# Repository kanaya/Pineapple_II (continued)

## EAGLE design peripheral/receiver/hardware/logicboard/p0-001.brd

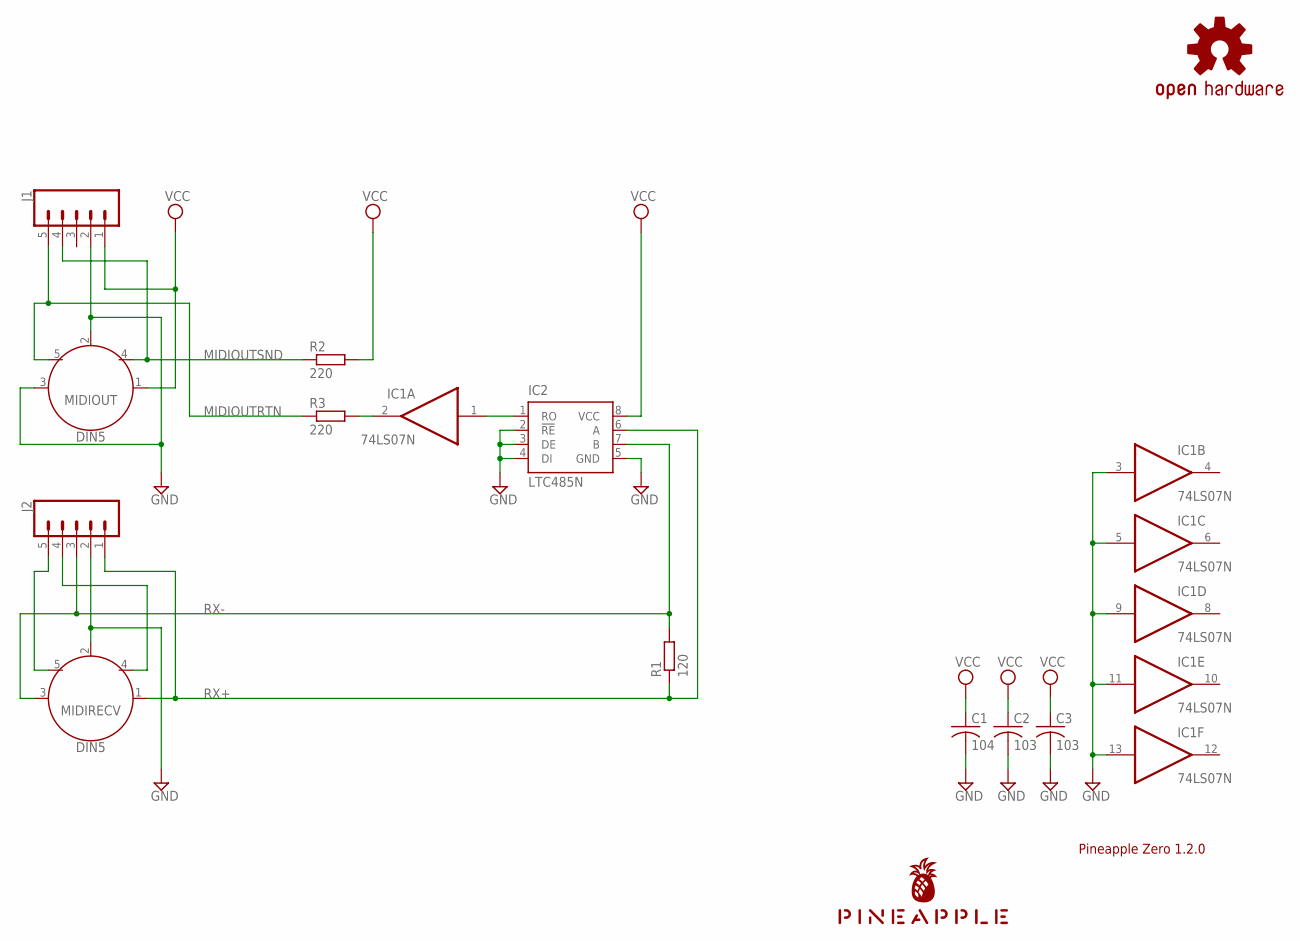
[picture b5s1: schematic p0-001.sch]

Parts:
C1: 104; C025-025X050
C2, C3: 103; C025-025X050
IC1: 74LS07N; DIL14
IC2: LTC485N; DIL08
J1, J2: CONN_05JST; JST-5-PTH
LOGO1: OSHW-LOGOS-COPPER; OSHW-LOGO-S_COPPER
MIDIOUT: DIN5; DIN5-RA-PTH
MIDIRECV: DIN5; DIN5-RA-PTH
R1: 120; 0204/5
R2, R3: 220; 0204/5
U$1: PINEAPPLE450

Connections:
DUMMY4: J2.4, MIDIRECV.4
DUMMY5: J2.5, MIDIRECV.5
GND: C1.2, C2.2, C3.2, IC1.3 (I), IC1.5 (I), IC1.7 (GND), IC1.9 (I), IC1.11 (I), IC1.13 (I), IC2.2 (!RE), IC2.3 (DE), IC2.4 (DI), IC2.5 (GND), J1.2, J2.2, MIDIOUT.2, MIDIOUT.3, MIDIRECV.2
MIDIOUTRTN: J1.5, MIDIOUT.5, R3.1
MIDIOUTSND: J1.4, MIDIOUT.4, R2.1
unnamed: IC1.2 (O), R3.2
RX+: IC2.6 (A), J2.1, MIDIRECV.1, R1.1
RX-: IC2.7 (B), J2.3, MIDIRECV.3, R1.2
TX: IC1.1 (I), IC2.1 (RO)
VCC: C1.1, C2.1, C3.1, IC1.14 (VCC), IC2.8 (VCC), J1.1, MIDIOUT.1, R2.2

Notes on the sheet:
Pineapple Zero 1.2.0

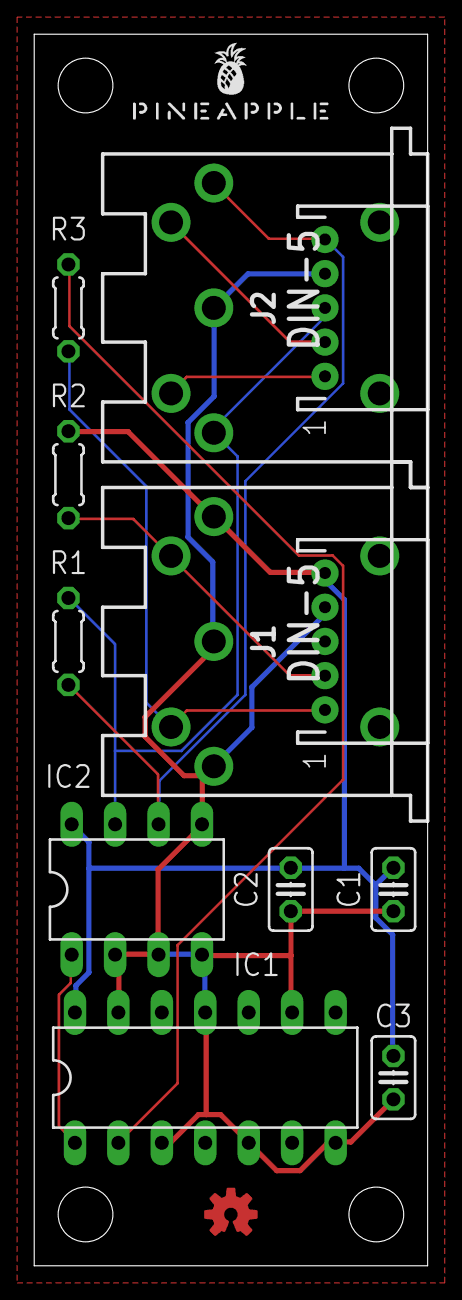
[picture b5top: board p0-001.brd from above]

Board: 2 copper layers, 23.0 x 72.0 mm, 14 parts (0 on the bottom side), 10 nets.

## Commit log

2020-01-31 Copied 2.0.0-X1 from the old repo.
2020-01-31 Added .gitignore.
2020-01-31 Changed panel design.
2020-01-31 New design for 2.0.1.
2020-01-31 Readability.
2020-01-31 Silk.
2020-02-01 Fixed power supply.
2020-02-08 Fixed position of large capacitors.
2020-02-09 Unified all buses.
2020-02-09 Now front LED is bi-color.
2020-02-09 PH connector.
2020-02-09 Document.
2020-02-09 Document update.
2020-02-09 Now pin 3 of MIDI In+ is connected to PUP pin.
2020-02-10 MIDI In detector.
2020-02-10 Added MIDI receiver unit.
2020-02-11 Moved peripheral dir to the top.
2020-02-12 Now U1 can be ether 1-Wire or Analog thermal sensor.
2020-02-12 Pin 25 of Front Connector is now connected to LED0.
2020-02-12 Document update for pull-down version.
2020-02-12 Now the sensors are connected to pull-down resistors.
2020-02-12 Silk and document.
2020-02-13 Qwiic (3.3V I2C) connector and signal level converter at the back surface.
2020-02-13 DC-In connector.
2020-02-14 Fine tune of silk.
2020-02-14 Set vRestrict zones.
2020-02-14 Changed vRestricted zones.
2020-02-14 Routed.
2020-02-14 Minor change of silk and vRestrict zones.
2020-02-14 Qwiic 5V.
2020-02-18 Pull up of RX.
2020-02-18 Pinhead for Relay.
2020-02-29 Clean up of document, schematic, and board design.
2020-02-29 Name of signal.
2020-03-01 GND net.
2020-03-23 Now MIDI In+ has Aux pin.
2020-03-24 Pull-down resistor from 100 to 10k.
2020-03-24 Changed pinout of Display port.
2020-04-18 F25 is now connected to AREF.
2020-04-19 Reflesh.
2020-04-21 Reflesh...
2020-04-27 Making...
2020-04-28 Now front port is Pineapple IIc compatible.
2020-04-29 Replacing.
2020-04-30 Refine.
2020-05-06 Renumbered number of jumpers.
2020-05-06 Now Vcc is directly connected to the regulator.
2020-05-07 Changed resistance attached to LED.
2020-05-07 Changed position of capacitors.
2020-05-11 Designing.
2020-05-11 Placed RTC board.
2020-05-11 To be renumbered.
2020-05-11 Renumbered.
2020-05-12 Fixed part numbers and silks.
2020-05-12 Fixed silk.
2020-05-12 Fixed pattern of RTC.
2020-05-13 Removed RLY con. Removed +9V con. Added I2C and Vdd con.
2020-05-13 Changed connectors of longrange receiver.
2020-05-15 Yeah!
2020-05-16 Looks good.
2020-05-17 First try.
2020-05-17 Fixed some error.
2020-05-19 New display connector.
2020-05-19 Re-design.
2020-05-19 Removed bus.
2020-05-19 A little bit better.
2020-05-20 Redesign...
2020-05-20 Rough design. Looks okay.
2020-06-02 Changed power supply.
2020-06-03 Added power selector.
2020-06-04 Added relay-out connector (again).
2020-06-28 Rounded corners.
2020-07-06 Added Vin mark on the board.
2020-07-08 Added Power-Grid.
2020-07-09 Power Grid 2.
2020-07-09 Swapped Vcc and Vcc/2.
2020-07-11 Fixed some errors.
2020-07-11 Changed Relay port and Alt. Power port.
2020-07-15 List of components.
2020-09-03 Added pads to connect MIDI IN and RX.
2020-09-03 Renumbered connectors. Fixed error of silk pattern.
2020-09-03 Update document.
2020-09-03 Fixed LED numbers.
2020-09-03 Simulation of Arduino Nano and Portena.
2020-09-03 Clean up of schematic.
2020-09-04 Moved resistor net up.
2020-09-18 Added LED pins. Changed pin number of LED connectors.
2020-09-24 Now B5 is connected to LED0 signal.
2020-09-24 B05 is connected to LED0A (not LED0).
2020-09-25 Analog input pins are now directly connected to pull-down resistor. Sensor pins are connected to analog input pins through analog switches. AREF is now connected to Vcc/2.
2020-09-25 Fixed AREF. Changed PWR connector. Etc.
2020-12-11 Test.
2021-02-16 Fixed pinout.
2021-02-18 Added SPI connector.
2021-02-19 Changed power pin from GND-Vcc to Vcc-GND-V+.
2021-02-19 Silk. (Tentative)
2021-02-22 Changed front-bus and SPI bus.
2021-02-24 Created P20 (port replicator) schematic and artwork.
2021-02-24 Cleared unnecessary parts.
2021-02-24 Parts only. No connection.
2021-02-24 The first artwork for MIDI Port Replicator.
2021-02-24 Re-arrange of net resistors.
2021-02-24 Silk of board.
2021-02-24 Remake of port rep.
2021-02-24 Hmm...
2021-02-24 Fix of _main_ logic board.
2021-02-24 Trying to implement a port replicator.
2021-02-24 Initial layout.
2021-02-27 Design of the port replicator.
2021-03-01 Silk mark for MIDI-IN.
2021-03-01 Silk mark for MIDI OUT.
2021-03-01 Approved warnings and added silk pattern for Vdd.
2021-03-01 Port replicator.
2021-03-05 Changed revision name to 2.1.0-RELEASE.
2021-03-08 Version of MIDI-IN, MIDI-THRU, and SPI only.
2021-03-08 Writing.
2021-03-08 Wiring.
2021-03-09 First working version of MIDI IN, MIDI THRU, SPI edition.
2021-03-09 Set restricted zones to left and right edges.
2021-03-09 GND.
2021-03-09 Arrangement of some parts (P20).
2021-03-10 DIP SW.
2021-03-10 Removed PWR pins.
2021-03-10 Clean up.
2021-03-13 JP5 is now compatible with Euroblock.
2021-03-13 The port replicator now has euroblock terminal.
2021-03-13 Renewal of Port Replicator.
2021-03-16 Moved relay port.
2021-03-18 Stepper Driver v0.0.2-X.
2021-03-19 Second try.
2021-03-20 TLP552 -> TLP2630.
2021-03-21 Pads to close V+ and Vin.
2021-03-26 Updated backside port to 2.0.
2021-03-27 Copied P2-001 to P2-003.
2021-03-28 Very rough but should be okay.
2021-03-28 Hotfix of the original P2.
2021-03-28 Configuring.
2021-03-29 Hotfix of relay connector (P2).
2021-03-29 First try. Should work. Need to renumber and rename parts.
2021-03-29 Renumbered some connectors.
2021-03-29 Moved Pineapple IIb to an independent repo.
2021-03-30 Flipped V+-Vin pads.
2021-03-30 Removed SE/Lucent-P1.
2021-04-02 Swapped MIDI RX+ and MIDI RX DETECT.
2021-04-02 Renumbered parts of Port Replicator.
2021-04-06 Fixed unconnected bus.
2021-04-10 Redesign of port rep.
2021-04-10 Renumbered parts of Pineapple II.
2021-04-10 Renumbered parts of Pineapple II and port rep.
2021-04-10 Renumbered Qwiic connectors.
2021-04-10 LED -> L.
2021-05-03 Fixed DTCT circuits.
2021-05-19 Silk for the lot number 2. Added Gerber.
2021-10-31 Now power has 12mil width and superpower has 24mil width.
2021-10-31 Power has 20mil width and superpower has 40mil width.
2021-10-31 Updated backport pintouts of port rep.
2021-10-31 Fixed netclasses.
2021-10-31 Added LED00 for indicating VCC/2.
2021-11-07 LED0->LED1, LED1->LED2.
2021-11-07 LED0->LED1, LED1->LED2, LED4->LED0.
2021-11-08 Added Vcc/2 Monitor.
2021-11-08 Now Pin A4 is MNTR and connected to Vcc/2 via Optocoupler.
2021-11-09 Swapped names of RN1 and RN2.
2021-11-10 Added silk pattern for LED00.
2021-11-10 Radius of restrict zone is now 2.25, not 2.23...
2021-11-11 Rastnet.
2021-11-12 Check up and silk.
2021-11-12 Fixed silk of backside.
2021-11-21 Removed port replicator.
2021-11-24 Renumbered signals and silk patterns.
2021-11-29 Removed JP4.
2021-11-29 Added silk of JP4.
2021-11-29 Re-arranged GeekPort 2.0.
2021-11-30 Redesigned BackPort.
2021-11-30 BackPort II.
2021-12-01 GND pattern.
2021-12-13 Changed signal name from RXDTCT to NDX.
2021-12-17 Fixed backside silk.
2022-01-29 Modified backside silk for better readability.
2022-01-29 Revision number.
2022-02-02 Added restricted zone.
2022-02-02 2021->2022.
2022-02-11 Changed resistance of R4 and R5 for LEDs.
2022-06-01 Counted up the release number (silk only).
2022-08-02 Now J4 is 3-pin connector.
2022-08-02 Moved J4.
2022-08-02 Autorouted.
2022-08-02 Autoroute and GND.
2022-08-16 6p SPI bus, 4p GPIO bus.
2022-08-16 Fixed GPIO connection.
2022-08-29 Arrange of J5 and JP5.
2022-08-29 Arrangement of J5 and JP5.
2022-09-13 Another GPIO port.
2022-09-14 Position of PWR pins.
2022-09-16 Positions of PWR and PWRSEL.
2022-10-15 Changed positions of lower components.
2022-10-15 Now the design passes DRC.
2022-10-15 Moved Fuse by 0.25mm.
2022-10-15 Moved backside components slightly.
2022-10-16 Panel design.
2022-10-16 Nothing is changed.
2022-10-16 Changed dimensions of panel holes.
2022-10-16 Fixed minor error of panel design.
2022-10-16 Fixed minor error (again) of the panel design.
2022-10-16 Fixed error of the panel design.
2022-10-16 Another design of the back panel (3b).
2022-10-16 Fixed error of panel design.
2022-10-17 Fixed LED size of the panel.
2022-10-22 Fixed fonts of the panel.
2022-10-23 PDF version of panel layouts.
2022-10-23 Fixed panel design.
2022-10-24 Fixed location of the logos.
2022-11-09 Added Takachi's plan.
2022-11-13 New panel design. (Trial)
